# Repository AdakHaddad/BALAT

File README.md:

# BALAT RTL — Road-Aware Livestock Guidance

An FPGA-first research and prototyping project for an autonomous livestock wearable.
The initial prototype uses standalone synthesizable RTL on a Digilent Basys 3 (Artix-7),
with external GNSS input and an interchangeable, output-oriented cue module.

> Status: architecture baseline plus a synthetic-trace Basys 3 bench demo and a
> Basys 3 USB-UART record and peer-summary bridge verified on hardware. GNSS
> input, map memory, and animal guidance effectiveness are not yet validated. A
> separate post-v0.1 software POC studies gatewayless collar communication; it
> does not change the v0.1 safety path.

## Initial design decision

**BALAT v0.1 does not include a SoC or soft CPU.** The FPGA implements a deterministic
data path:

```text
GNSS UART
   |
   v
GNSS parser --> position/quality registers
   |
   v
Road-segment memory (BRAM / initialized ROM)
   |
   v
Road geometry + distance engine
   |
   v
Trajectory / approach estimator
   |
   v
Risk state machine
   |
   v
Cue scheduler / output driver
   |
   v
MCI output connector --> external cue driver/module
```

An MCU, processor, radio, cloud connection, camera, movement classifier, and bidirectional
cue-module protocol are explicitly out of scope for v0.1 unless later justified by evidence.

## Repository map

- `PRD.md` — product requirements and acceptance criteria.
- `ARCHITECTURE.md` — functional and RTL architecture.
- `PLAN.md` — milestones, tasks, and exit criteria.
- `AGENTS.md` — instructions for human and AI coding agents.
- `docs/INTERFACES.md` — GNSS, road-map, and cue interface contracts.
- `docs/VERIFICATION.md` — simulation, FPGA, and field-test strategy.
- `docs/SAFETY_AND_LIMITATIONS.md` — safety constraints and known limitations.
- `docs/RESEARCH_NOTES.md` — research questions and evidence to collect.
- `docs/DECISIONS.md` — architecture decision records.
- `docs/BASYS3_DEMO.md` — build, program, and run the synthetic-trace demo.
- `docs/PROTOTYPE_RUNBOOK.md` — improve the FPGA prototype toward a real-GNSS lab demonstrator.
- `docs/MICROCONTROLLER_PROTOTYPE.md` — parallel MCU prototype for GNSS, power, logging, and field-data validation.
- `docs/HERDSYNC_POC.md` — post-v0.1 gatewayless DTN software POC and hardware plan.
- `docs/BASYS3_HERDSYNC_BRIDGE.md` — Basys 3 USB-UART record bridge and host collector.
- `rtl/` — synthesizable Verilog/SystemVerilog.
- `tb/` — testbenches.
- `constraints/` — Basys 3 XDC constraints.
- `scripts/` — build and data-conversion scripts.
- `poc/herdsync_dtn/` — HerdSync-DTN reference model, scenarios, UART frame codec, and host collector.
- `poc/tests/` — POC unit and scenario tests.
- `data/` — sample map data and generated road-segment memory images.

## Quick start

1. Read `PRD.md`, `ARCHITECTURE.md`, and `docs/SAFETY_AND_LIMITATIONS.md`.
2. Confirm the Basys 3 board revision and Vivado version.
3. Implement and simulate the GNSS parser before connecting physical hardware.
4. Start with synthetic road segments and a host-driven UART test.
5. Add the geometry and risk pipeline only after parser tests pass.
6. Use a dummy LED/buzzer load before connecting any actuator driver.
7. Build and run the current synthetic-trace demo with `docs/BASYS3_DEMO.md`.
8. Follow `docs/PROTOTYPE_RUNBOOK.md` before describing a real-GNSS or map-aware FPGA demo.
9. Use `docs/MICROCONTROLLER_PROTOTYPE.md` for a parallel wearable and field-data prototype.
10. Optionally run the post-v0.1 HerdSync-DTN simulation:
   `python3 -m poc.herdsync_dtn --scenario all`; see `docs/HERDSYNC_POC.md`.
11. Stream frames from the Basys 3 to a PC and back with
   `docs/BASYS3_HERDSYNC_BRIDGE.md`.

## Design principles

1. Autonomous core: no base station or internet required during runtime.
2. Map-first: roads are preloaded/configured from an external map workflow; no live map API in the wearable.
3. Conservative risk: account for GNSS uncertainty and stale fixes.
4. Output-only cue module in v0.1: BALAT commands an external driver; it does not assume actuator feedback.
5. Humane-by-design: cues are experimental, conditioned, limited, and subject to supervised animal-behaviour validation.
6. Reproducible engineering: every module has a specification, testbench, and measurable acceptance criteria.

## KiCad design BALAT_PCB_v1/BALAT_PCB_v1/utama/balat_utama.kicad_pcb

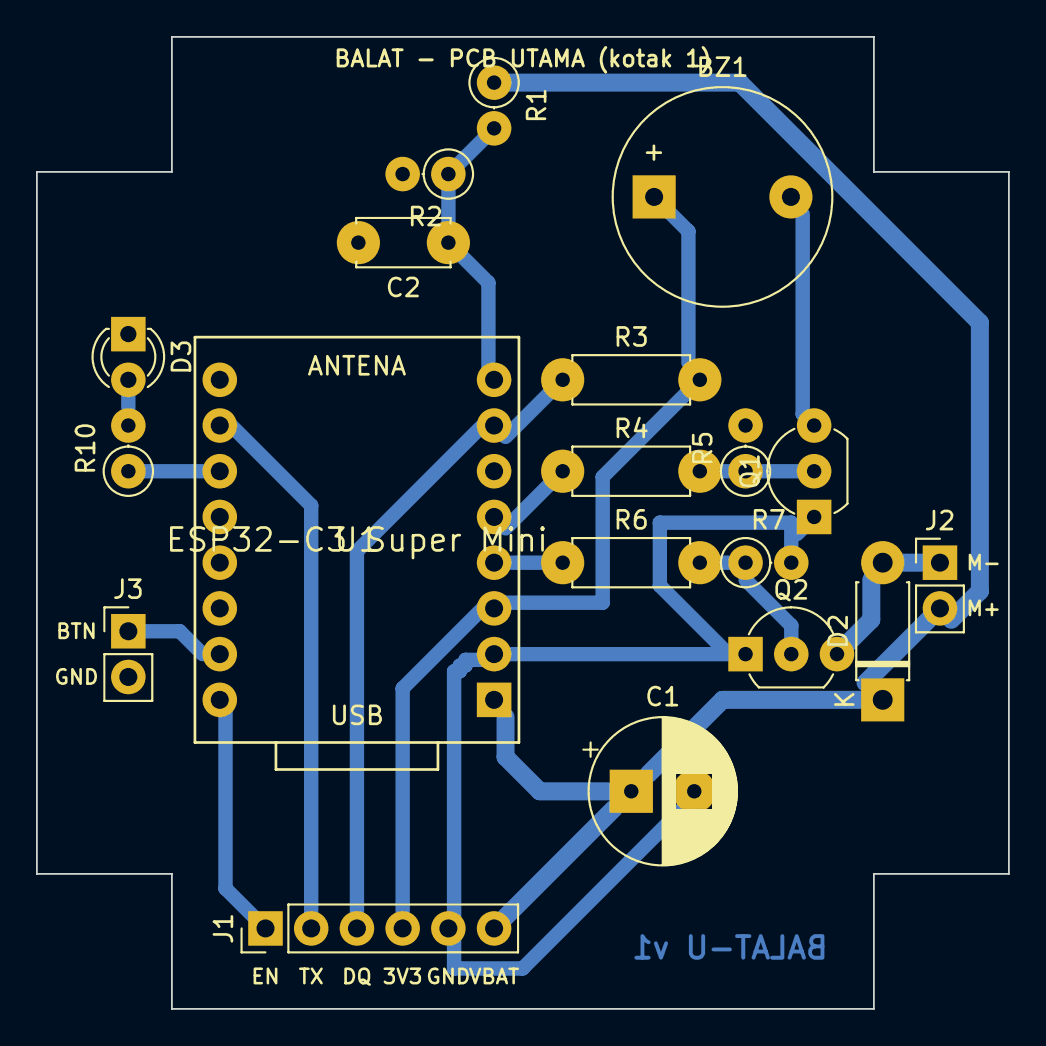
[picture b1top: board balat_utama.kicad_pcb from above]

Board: 2 copper layers, 54.0 x 54.0 mm, 19 parts (0 on the bottom side), 16 nets.

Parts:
BZ1: Buzzer aktif 3,3V; Buzzer_12x9.5RM7.6
C1: 470uF 10V; CP_Radial_D8.0mm_P3.50mm
C2: 100nF; C_Disc_D5.0mm_W2.5mm_P5.00mm
D2: 1N5819; D_DO-41_SOD81_P7.62mm_Horizontal
D3: LED; LED_D3.0mm
J1: Ke kotak 2; PinHeader_1x06_P2.54mm_Vertical
J2: Motor PS; PinHeader_1x02_P2.54mm_Vertical
J3: Tombol lapor; PinHeader_1x02_P2.54mm_Vertical
Q1: S8050; TO-92_Inline_Wide
Q2: 2N2222; TO-92_Inline_Wide
R1, R2: 100k; R_Axial_DIN0207_L6.3mm_D2.5mm_P2.54mm_Vertical
R3: 4k7; R_Axial_DIN0207_L6.3mm_D2.5mm_P7.62mm_Horizontal
R4: 1k; R_Axial_DIN0207_L6.3mm_D2.5mm_P7.62mm_Horizontal
R5, R7: 10k; R_Axial_DIN0207_L6.3mm_D2.5mm_P2.54mm_Vertical
R6: 470; R_Axial_DIN0207_L6.3mm_D2.5mm_P7.62mm_Horizontal
R10: 220; R_Axial_DIN0207_L6.3mm_D2.5mm_P2.54mm_Vertical
U1: ESP32-C3 Super Mini; ESP32-C3_SuperMini

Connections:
3V3: BZ1.1, J1.4, R3.2, U1.3V3
BTN: J3.1, U1.IO6
BUZ_CTRL: R4.1, U1.IO3
BUZ_N: BZ1.2, Q1.3
GND: C1.2, C2.2, D3.1, J1.5, J3.2, Q1.1, Q2.1, R2.2, R5.2, R7.2, U1.GND
GPS_EN: J1.1, U1.IO5
GPS_TX: J1.2, U1.IO20
LED_A: D3.2, R10.2
LED_CTRL: R10.1, U1.IO10
MOT_CTRL: R6.1, U1.IO4
MOT_N: D2.2, J2.1, Q2.3
Q1_B: Q1.2, R4.2, R5.1
Q2_B: Q2.2, R6.2, R7.1
TEMP_DQ: J1.3, R3.1, U1.IO1
VBAT: C1.1, D2.1, J1.6, J2.2, R1.1, U1.5V
VBAT_SENSE: C2.1, R1.2, R2.1, U1.IO0

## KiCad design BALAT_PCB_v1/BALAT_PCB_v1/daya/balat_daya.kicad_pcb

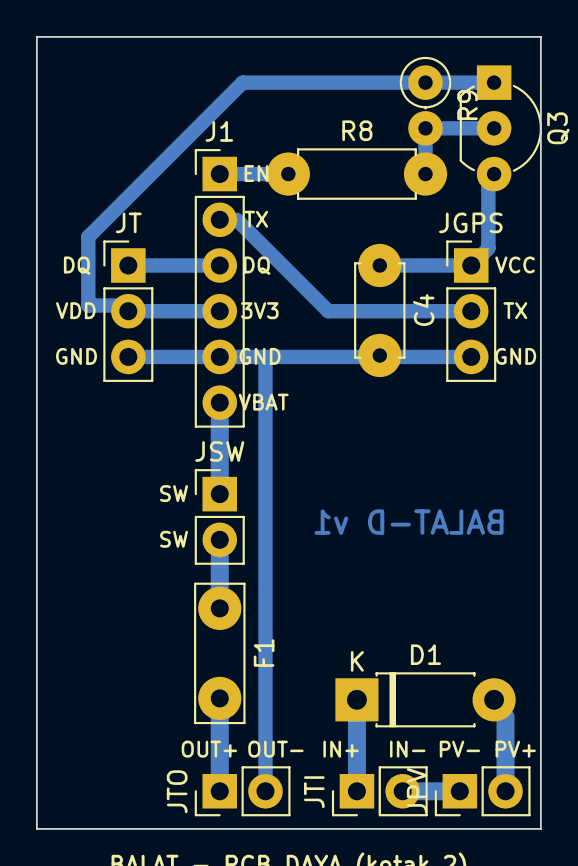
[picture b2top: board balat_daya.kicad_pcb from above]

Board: 2 copper layers, 28.0 x 44.0 mm, 13 parts (0 on the bottom side), 13 nets.

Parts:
C4: 100nF; C_Disc_D5.0mm_W2.5mm_P5.00mm
D1: 1N5819; D_DO-41_SOD81_P7.62mm_Horizontal
F1: Polyfuse 1A; C_Disc_D7.5mm_W2.5mm_P5.00mm
J1: Ke kotak 1; PinHeader_1x06_P2.54mm_Vertical
JGPS: GPS NEO-6M; PinHeader_1x03_P2.54mm_Vertical
JPV: Panel surya; PinHeader_1x02_P2.54mm_Vertical
JSW: Saklar ON/OFF; PinHeader_1x02_P2.54mm_Vertical
JT: DS18B20 (kabel); PinHeader_1x03_P2.54mm_Vertical
JTI: TP4056 IN; PinHeader_1x02_P2.54mm_Vertical
JTO: TP4056 OUT; PinHeader_1x02_P2.54mm_Vertical
Q3: S8550; TO-92_Inline_Wide
R8: 1k; R_Axial_DIN0207_L6.3mm_D2.5mm_P7.62mm_Horizontal
R9: 10k; R_Axial_DIN0207_L6.3mm_D2.5mm_P2.54mm_Vertical

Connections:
3V3: J1.4, JT.2, Q3.1, R9.1
FUSED: F1.1, JSW.2
GND: C4.2, J1.5, JGPS.3, JT.3, JTO.2
GPS_EN: J1.1, R8.1
GPS_TX: J1.2, JGPS.2
GPS_VCC: C4.1, JGPS.1, Q3.3
PV_MIN: JPV.1, JTI.2
Q3_B: Q3.2, R8.2, R9.2
SOLAR_IN: D1.1, JTI.1
SOLAR_RAW: D1.2, JPV.2
TEMP_DQ: J1.3, JT.1
TP_OUT: F1.2, JTO.1
VBAT: J1.6, JSW.1
